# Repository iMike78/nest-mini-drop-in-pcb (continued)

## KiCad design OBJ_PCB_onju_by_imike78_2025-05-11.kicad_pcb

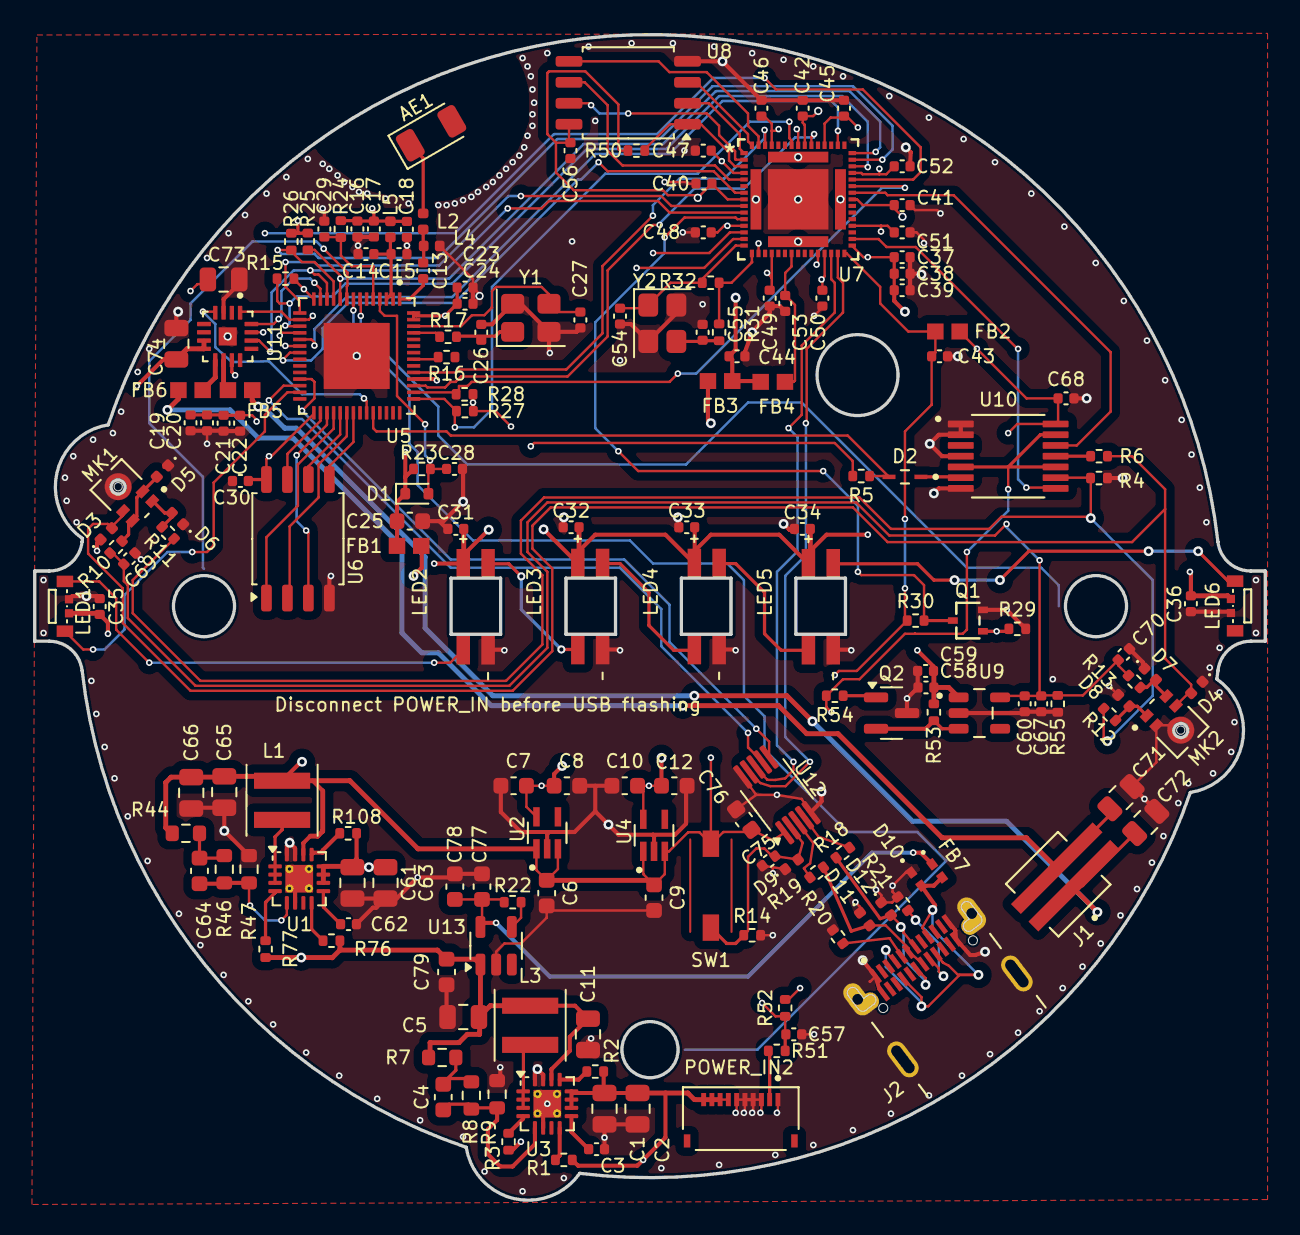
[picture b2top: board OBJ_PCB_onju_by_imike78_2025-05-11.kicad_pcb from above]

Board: 4 copper layers, 74.5 x 70.6 mm, 177 parts (0 on the bottom side), 106 nets.

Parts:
AE1: 2450AT18A100E; Johanson_2450AT18x100
C1, C5, C61, C65: 22uF; C_0805_2012Metric
C2, C63: 10uF; C_0805_2012Metric
C3, C62: 10nF; C_0402_1005Metric
C4, C64: 220pF; C_0603_1608Metric
C6, C9: 2.2uF; C_0603_1608Metric
C7, C10, C78: 4.7uF; C_0603_1608Metric
C8, C12, C25, C76, C77, C79: 100nF; C_0603_1608Metric
C11, C66, C73: 100nF; C_0805_2012Metric
C13: 1.2pF; C_0402_1005Metric
C14: 2.4pF; C_0402_1005Metric
C15, C16, C19, C20, C21, C23, C30, C31, C32, C33, C34, C35, C36, C37, C38, C39, C40, C41, C42, C43, C45, C46, C47, C48, C49, C50, C51, C52, C56, C57, C58, C67, C68, C69, C70, C75: 100nF; C_0402_1005Metric
C17, C22, C24, C28, C44, C53, C60: 1uF; C_0402_1005Metric
C18: 10uF; C_0402_1005Metric
C26, C27, C29: 12pF; C_0402_1005Metric
C54, C55: 20pF; C_0402_1005Metric
C59: 2.2uF; C_0402_1005Metric
C71, C72: 10nF; C_0805_2012Metric
C74: 47uF; C_0805_2012Metric
D1: LRB520S-30T1G; D_SOD-523
D2: RB521S30T1G; DIOM168X70N
D3, D4, D5, D6, D7, D8, D9, D11, D12: PESD0402V05; D_0402_1005Metric
D10: TPD1E10B06DPYR; TPD1E05U06DPYR
FB1, FB2: 120R; BLM18PG121SN1D
FB3, FB4, FB5, FB6: 600R; BLM18PG121SN1D
FB7: 0R; TPD1E05U06DPYR
J1: 1775443-2
J2: usb_c
L1, L3: 2.2uH; L_Coilcraft_XxL4020
L2: 3.3nH; L_0402_1005Metric
L4: 2.7nH; L_0402_1005Metric
L5: 2.2nH; L_0402_1005Metric
LED1, LED6: SK6812D-EC3210R; LED-SMD_4P_SK6812D-EC3210R
LED2, LED3, LED4, LED5: SK6812MINI-E
MK1, MK2: T3902; MIC_T3902
POWER_IN2: FH34SRJ-10S-0.5SH_50_; HRS_FH34SRJ-10S-0.5SH_50_
Q1: LBSS138WT1G; SC-70-3_L2.1-W1.3-P0.65-LS2.1-BR
Q2: BC847B; SOT-23
R1, R2, R3, R22, R30, R76, R77, R108: 100k; R_0402_1005Metric
R4, R29, R55: 47k; R_0402_1005Metric
R5, R14, R23, R24: 10k; R_0402_1005Metric
R6, R10, R11, R12, R13, R51: 100R; R_0402_1005Metric
R7, R44: 49.9R; R_0603_1608Metric
R8: 210k; R_0603_1608Metric
R9: 40k; R_0603_1608Metric
R15, R17: 0R; R_0402_1005Metric
R16: 499R; R_0402_1005Metric
R18, R19: 22R; R_0402_1005Metric
R20, R21: 5.1k; R_0402_1005Metric
R25, R26, R27, R28, R50: 4.7k; R_0402_1005Metric
R31: 680R; R_0402_1005Metric
R32: 1M; R_0402_1005Metric
R46: 100k; R_0603_1608Metric
R47: 22.1k; R_0603_1608Metric
R52: 1k; R_0402_1005Metric
R53: 470k; R_0402_1005Metric
R54: 3.3k; R_0402_1005Metric
SW1: SMXS‑01K‑TP; CHS-01TA
U1, U3: TPS62130; VQFN-16-1EP_3x3mm_P0.5mm_EP1.68x1.68mm_ThermalVias
U2: MIC5365-1.8YC5-TR; SOT65P210X110-5N
U4: MIC5365-0.9YC5-TR; SOT65P210X110-5N
U5: ESP32-S3R8; QFN40P700X700X90-57N
U6, U8: W25Q128JVSIQ; SOIC-8_5.3x5.3mm_P1.27mm
U7: XU316-1024-QF60B-C24
U9: TLV73333PDBVR
U10: SN74LVC125APWR; SOP65P640X120-14N
U11: MAX98357AETE_T; max98357aete
U12: FSUSB42MUX; MSOP-10_3x3mm_P0.5mm
U13: AP22802AW5-7; SOT-23-5
Y1: 40MHz; Crystal_SMD_3225-4Pin_3.2x2.5mm
Y2: 24MHz; Crystal_SMD_3225-4Pin_3.2x2.5mm

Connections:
+0V9: C10.1, C12.1, FB3.1, U4.5 (VOUT)
+1V8: C7.1, C8.1, C37.1, C38.1, C39.1, U2.5 (VOUT), U7.17 (VDDIOB18), U7.26 (VDDIOB18), U7.31 (USB_VDD18)
+3V3: C6.1, C9.1, C43.1, C65.1, C66.1, C76.1, FB1.1, FB2.1, L1.2, R30.1, R44.1, SW1.SI, U1.14 (VOS), U2.1 (VIN), U2.3 (EN), U4.1 (VIN), U4.3 (EN), U7.30 (USB_VDD33), U12.1 (VCC)
+5V: C5.1, C11.1, C31.1, C32.1, C33.1, C34.1, C35.1, C36.1, C58.1, C59.1, C61.1, C63.1, C73.1, C74.1, C79.1, L3.2, LED1.4 (VDD), LED2.1 (VDD), LED3.1 (VDD), LED4.1 (VDD), LED5.1 (VDD), LED6.4 (VDD), R7.1, R53.2, R76.1, R77.1, R108.1, U1.10 (VIN), U1.11 (VIN), U1.12 (VIN), U3.14 (VOS), U9.1 (IN), U11.7 (VDD), U11.8 (VDD), U13.1 (OUT)
+14V: C1.1, C2.1, POWER_IN2.7, POWER_IN2.8, POWER_IN2.9, POWER_IN2.10, R1.1, R2.1, R3.1, U3.10 (VIN), U3.11 (VIN), U3.12 (VIN)
/ESP32-S3R8/SPI_CLK: U5.33 (SPICLK), U6.6 (CLK)
/ESP32-S3R8/SPI_CS0: U5.32 (SPICS0), U6.1 (~CS)
/ESP32-S3R8/SPI_D: U5.35 (SPID), U6.5 (DI/IO_{0})
/ESP32-S3R8/SPI_HD: U5.30 (SPIHD), U6.7 (~HOLD/~RESET/IO_{3})
/ESP32-S3R8/SPI_Q: U5.34 (SPIQ), U6.2 (DO/IO_{1})
/ESP32-S3R8/SPI_WP: U5.31 (SPIWP), U6.3 (~WP/IO_{2})
/Power/USB_D_N: D12.2 (A2), J2.A7 (DN1), J2.B7 (DN2), R18.1
/Power/USB_D_P: D11.2 (A2), J2.A6 (DP1), J2.B6 (DP2), R19.1
/Power/USB_IN_D_N: R18.2, U12.4 (D-)
/Power/USB_IN_D_P: R19.2, U12.3 (D+)
/Power/USB_SEL: C75.1, D9.2 (A2), R14.1, SW1.S0, U12.2 (SEL)
/XMOS/MIC_CLK: U7.39 (X1D22), U10.12 (4A)
/XMOS/MIC_CLK_M: D3.2 (A2), D4.2 (A2), MK1.4 (CLK), MK2.4 (CLK), R6.1
/XMOS/MIC_DATA: U7.32 (X1D13), U10.8 (3Y)
/XMOS/MIC_DATA_M: R4.2, R11.1, R12.1, U10.9 (3A)
/XMOS/QSPI_CLK: U7.5 (X0D10), U8.6 (CLK)
/XMOS/QSPI_CS_N: R50.1, U7.3 (X0D01), U8.1 (~CS)
/XMOS/QSPI_D0: U7.59 (X0D04), U8.5 (DI/IO_{0})
/XMOS/QSPI_D1: U7.1 (X0D05), U8.2 (DO/IO_{1})
/XMOS/QSPI_D2: U7.60 (X0D06), U8.3 (~WP/IO_{2})
/XMOS/QSPI_D3: U7.2 (X0D07), U8.7 (~HOLD/~RESET/IO_{3})
/XMOS/VBUS_DETEC: Q1.3 (D), R30.2, U7.11 (X1D09)
AUDIO_PA_EN: U5.37 (SPICLK_P), U11.4 (SD_MODE)
ESP_3V3: C16.1, C17.1, C18.1, C19.1, C20.1, C21.1, C22.1, C23.2, C24.2, C25.1, C30.1, D1.1 (K), FB1.2, L5.2, R5.2, R23.1, R24.1, R25.1, R26.1, R27.1, R28.1, U5.20 (VDD3P3_RTC), U5.29 (VDD_SPI), U5.46 (VDD3P3_CPU), U5.55 (VDDA1), U5.56 (VDDA2), U6.8 (VCC)
ESP_BOOT: C29.1, R24.2, U5.5 (GPIO0)
ESP_IO40: U5.45 (MTDO), U7.51 (X0D43)
ESP_IO41: U5.47 (MTDI), U7.58 (X0D33)
ESP_MUTE_DET: D2.2, R5.1, U5.38 (GPIO33)
ESP_RST: C28.1, D1.2 (A), R23.2, U5.4 (CHIP_PU)
ESP_USB_N: U5.25 (GPIO19), U12.6 (HSD1-)
ESP_USB_P: U5.26 (GPIO20), U12.7 (HSD1+)
ESP_WS2812: LED1.3 (DIN), U5.27 (GPIO21)
GND: C1.2, C2.2, C3.1, C5.2, C6.2, C7.2, C8.2, C9.2, C10.2, C11.2, C12.2, C14.2, C15.2, C16.2, C17.2, C18.2, C19.2, C20.2, C21.2, C22.2, C23.1, C24.1, C25.2, C26.1, C27.1, C28.2, C29.2, C30.2, C31.2, C32.2, C33.2, C34.2, C35.2, C36.2, C37.2, C38.2, C39.2, C40.2, C41.2, C42.2, C43.2, C44.2, C45.2, C46.2, C47.2, C48.2, C49.2, C50.2, C51.2, C52.2, C53.2, C54.2, C55.2, C56.2, C57.2, C58.2, C59.2, C60.2, C61.2, C62.1, C63.2, C65.2, C66.2, C67.2, C68.2, C69.2, C70.2, C71.2, C72.2, C73.2, C74.2, C75.2, C76.2, C77.2, C78.2, C79.2, D3.1 (A1), D4.1 (A1), D5.1 (A1), D6.1 (A1), D7.1 (A1), D8.1 (A1), D9.1 (A1), D10.1 (A1), D11.1 (A1), D12.1 (A1), J2.A1 (GND_A), J2.A12 (GND_A), J2.B1 (GND_B), J2.B12 (GND_B), J2.SH1 (SHIELD), J2.SH2 (SHIELD), J2.SH3 (SHIELD), J2.SH4 (SHIELD), L4.1, LED1.1 (GND), LED2.3 (GND), LED3.3 (GND), LED4.3 (GND), LED5.3 (GND), LED6.1 (GND), MK1.3_1 (GND), MK1.3_2 (GND), MK2.2 (SELECT), MK2.3_1 (GND), MK2.3_2 (GND), POWER_IN2.1, POWER_IN2.3, POWER_IN2.4, POWER_IN2.5, POWER_IN2.6, Q1.2 (S), Q2.3 (E), R4.1, R9.2, R14.2, R20.2, R21.2, R29.2, R47.2, R55.1, U1.6 (GND), U1.15 (GND), U1.16 (GND), U1.17 (GND), U2.2 (GND), U3.6 (GND), U3.15 (GND), U3.16 (GND), U3.17 (GND), U4.2 (GND), U5.57 (GND), U6.4 (GND), U7.65 (VSS), U8.4 (GND), U9.2 (GND), U10.1 (1~OE), U10.2 (1A), U10.4 (2~OE), U10.7 (GND), U11.3 (GND), U11.11 (GND), U11.15 (GND), U11.17 (EP), U12.5 (GND), U12.10 (~OE), U13.2 (GND), Y1.2, Y1.4, Y2.2, Y2.4
I2C2_SCL: R28.2, U5.44 (MTCK), U7.40 (X0D29)
I2C2_SDA: R27.2, U5.43 (GPIO38), U7.54 (X0D30)
I2C_SCL: R26.2, U5.11 (GPIO6), U7.44 (X0D37)
I2C_SDA: R25.2, U5.10 (GPIO5), U7.45 (X0D38)
I2S2_BCLK: U5.18 (GPIO13), U7.41 (X0D35)
I2S2_DATA: U5.21 (XTAL_32K_P), U7.7 (X0D11)
I2S2_LRCLK: U5.19 (GPIO14), U7.47 (X0D39)
I2S2_MCLK: R15.1, U5.17 (GPIO12), U7.43 (X0D36)
I2S_BCLK: U5.13 (GPIO8), U7.13 (X1D10), U11.16 (BCLK)
I2S_DIN_ESP: U5.16 (GPIO11), U7.53 (X1D34), U11.1 (DIN)
I2S_DIN_SEC: U5.15 (GPIO10), U7.9 (X1D00)
I2S_LRCK: U5.12 (GPIO7), U7.10 (X1D01), U11.14 (LRCLK)
I2S_MCLK: R15.2, U5.14 (GPIO9), U7.14 (X1D11)
MUTE: POWER_IN2.2, R51.2
MUTE_ON: C57.1, R51.1, R52.1, R54.2, U10.5 (2A), U10.10 (3~OE), U10.13 (4~OE)
unnamed: AE1.1, L2.1
unnamed: C4.1, R7.2, R8.1
unnamed: C13.1, L2.2, L4.2
unnamed: C14.1, C15.1, L5.1, U5.2 (VDD3P3), U5.3 (VDD3P3)
unnamed: C26.2, R17.1, Y1.1
unnamed: C55.1, R31.2, Y2.3
unnamed: C64.1, R44.2, R46.1
unnamed: C71.1, FB6.2, J1.2
unnamed: C72.1, FB5.2, J1.1
unnamed: D5.2 (A2), MK1.2 (SELECT), MK1.5 (VDD), R10.2
unnamed: D6.2 (A2), MK1.1 (DATA), R11.2
unnamed: D7.2 (A2), MK2.5 (VDD), R13.2
unnamed: D8.2 (A2), MK2.1 (DATA), R12.2
unnamed: D10.2 (A2), FB7.2, J2.A4 (VBUS_A), J2.A9 (VBUS_A), J2.B4 (VBUS_B), J2.B9 (VBUS_B)
unnamed: J2.A5 (CC1), R20.1
unnamed: J2.B5 (CC2), R21.1
unnamed: L1.1, U1.1 (SW), U1.2 (SW), U1.3 (SW)
unnamed: L3.1, U3.1 (SW), U3.2 (SW), U3.3 (SW)
unnamed: LED1.2 (DOUT), LED2.4 (DIN)
unnamed: LED2.2 (DOUT), LED3.4 (DIN)
unnamed: LED3.2 (DOUT), LED4.4 (DIN)
unnamed: LED4.2 (DOUT), LED5.4 (DIN)
unnamed: LED5.2 (DOUT), LED6.3 (DIN)
unnamed: Q2.1 (B), R54.1
unnamed: Q2.2 (C), R53.1, U9.3 (EN)
unnamed: R76.2, U1.8 (DEF)
unnamed: R108.2, U1.13 (EN)
unnamed: C64.2, R46.2, R47.1, U1.5 (FB)
unnamed: R77.2, U1.4 (PG)
unnamed: C62.2, U1.9 (SS/TR)
unnamed: R1.2, U3.8 (DEF)
unnamed: R2.2, U3.13 (EN)
unnamed: C4.2, R8.2, R9.1, U3.5 (FB)
unnamed: R3.2, U3.4 (PG)
unnamed: C3.2, U3.9 (SS/TR)
unnamed: C13.2, U5.1 (LNA_IN)
unnamed: R16.2, U5.49 (U0TXD)
unnamed: R17.2, U5.53 (XTAL_N)
unnamed: C27.2, U5.54 (XTAL_P), Y1.3
unnamed: C53.1, FB4.1, U7.22 (PLL_AVDD)
unnamed: R31.1, R32.2, U7.16 (XIN)
unnamed: C54.1, R32.1, U7.15 (XOUT), Y2.1
unnamed: D2.1, U10.6 (2Y)
unnamed: R6.2, U10.11 (4Y)
unnamed: FB5.1, U11.10 (OUTN)
unnamed: FB6.1, U11.9 (OUTP)
unnamed: R22.1, U13.4 (EN)
VBUS: C77.1, C78.1, FB7.1, Q1.1 (G), R22.2, R29.1, U13.5 (IN)
VDD: C44.1, C45.1, C46.1, C47.1, C48.1, C49.1, C50.1, C51.1, C52.1, FB3.2, FB4.2, U7.4 (VDD), U7.12 (VDD), U7.19 (VDD), U7.27 (VDD), U7.34 (VDD), U7.42 (VDD), U7.49 (VDD), U7.57 (VDD), U7.61 (VDD), U7.62 (VDD), U7.63 (VDD), U7.64 (VDD)
VDDIO: C40.1, C41.1, C42.1, C56.1, C68.1, FB2.2, R50.2, R52.2, U7.8 (VDDIOL), U7.38 (VDDIOR), U7.52 (VDDIOT), U8.8 (VCC), U10.14 (VCC)
VDD_MIC: C60.1, C67.1, C69.1, C70.1, R10.1, R13.1, R55.2, U9.5 (OUT)
XMOS_USB_N: U7.28 (USB_DM), U12.8 (HSD2-)
XMOS_USB_P: U7.29 (USB_DP), U12.9 (HSD2+)

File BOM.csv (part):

Top Designator;Comment;Footprint;Part # ;Manufacturer;Footprint;Description;JLCPCB Part #
AE1;2450AT18A100E;Johanson_2450AT18x100;2450AT18A100E;Johanson Dielectrics;1206;0.5dBi 2.4G Antenna 2.4GHz 2W 1206 Antennas ROHS;C89334
C1,C5,C61,C65;22uF;805;CL21A226MAQNNNE;Samsung Electro-Mechanics;805;25V 22uF X5R ±20% 0805 Multilayer Ceramic Capacitors MLCC - SMD/SMT ROHS;C45783
C2,C63;10uF;805;CL21A106KAYNNNE;Samsung Electro-Mechanics;805;25V 10uF X5R ±10% 0805 Multilayer Ceramic Capacitors MLCC - SMD/SMT ROHS;C15850
C3,C62;10nF;402;CL05B103KB5NNNC;Samsung Electro-Mechanics;402;50V 10nF X7R ±10% 0402 Multilayer Ceramic Capacitors MLCC - SMD/SMT ROHS;C15195
C4,C64;220pF;603;CL10B221KB8NNNC;Samsung Electro-Mechanics;603;50V 220pF X7R ±10% 0603 Multilayer Ceramic Capacitors MLCC - SMD/SMT ROHS;C1603
C6,C9;2.2uF;603;CL10A225KO8NNNC;Samsung Electro-Mechanics;603;16V 2.2uF X5R ±10% 0603 Multilayer Ceramic Capacitors MLCC - SMD/SMT ROHS;C23630
C10,C7,C78;4.7uF;603;CL10A475KO8NNNC;Samsung Electro-Mechanics;603;16V 4.7uF X5R ±10% 0603 Multilayer Ceramic Capacitors MLCC - SMD/SMT ROHS;C19666
C11,C66,C73;100nF;805;CC0805KRX7R9BB104;YAGEO;805;50V 100nF X7R ±10% 0805 Multilayer Ceramic Capacitors MLCC - SMD/SMT ROHS;C49678
C12,C25,C76,C77,C79,C8;100nF;603;CC0603KRX7R9BB104;YAGEO;603;50V 100nF X7R ±10% 0603 Multilayer Ceramic Capacitors MLCC - SMD/SMT ROHS;C14663
C13;1.2pF;402;CC0402BRNPO9BN1R2;YAGEO;402;50V 1.2pF NP0 0402  Multilayer Ceramic Capacitors MLCC - SMD/SMT ROHS;C327292
C14;2.4pF;402;0402CG2R4C500NT;FH (Guangdong Fenghua Advanced Tech);402;50V 2.4pF C0G 0402  Multilayer Ceramic Capacitors MLCC - SMD/SMT ROHS;C48346
C15,C16,C19,C20,C21,C23,C30,C37,C38,C39,C40,C41,C42,C43,C45,C46,C47,C48,C49,C50,C51,C52,C56,C57,C58,C67,C68,C69,C70,C75;100nF;402;CL05B104KO5NNNC;Samsung Electro-Mechanics;402;16V 100nF X7R ±10% 0402 Multilayer Ceramic Capacitors MLCC - SMD/SMT ROHS;C1525
C31,C32,C33,C34,C35,C36;0.1uF;402;CL05B104KO5NNNC;Samsung Electro-Mechanics;402;16V 100nF X7R ±10% 0402 Multilayer Ceramic Capacitors MLCC - SMD/SMT ROHS;C1525
C17,C22,C24,C28,C44,C53,C60;1uF;402;CL05A105KA5NQNC;Samsung Electro-Mechanics;402;25V 1uF X5R ±10% 0402 Multilayer Ceramic Capacitors MLCC - SMD/SMT ROHS;C52923
C18;10uF;402;CL05A106MQ5NUNC;Samsung Electro-Mechanics;402;6.3V 10uF X5R ±20% 0402 Multilayer Ceramic Capacitors MLCC - SMD/SMT ROHS;C15525
C26,C27,C29;12pF;402;0402CG120J500NT;FH (Guangdong Fenghua Advanced Tech);402;50V 12pF C0G ±5% 0402 Multilayer Ceramic Capacitors MLCC - SMD/SMT ROHS;C1547
C54,C55;20pF;402;0402CG200J500NT;FH (Guangdong Fenghua Advanced Tech);402;50V 20pF C0G ±5% 0402 Multilayer Ceramic Capacitors MLCC - SMD/SMT ROHS;C1554
C59;2.2uF;402;CL05A225MQ5NSNC;Samsung Electro-Mechanics;402;6.3V 2.2uF X5R ±20% 0402 Multilayer Ceramic Capacitors MLCC - SMD/SMT ROHS;C12530
C71,C72;10nF;805;CL21B103KBANNNC;Samsung Electro-Mechanics;805;50V 10nF X7R ±10% 0805 Multilayer Ceramic Capacitors MLCC - SMD/SMT ROHS;C1710
C74;47uF;805;CL21A476MQYNNNE;Samsung Electro-Mechanics;805;6.3V 47uF X5R ±20% 0805 Multilayer Ceramic Capacitors MLCC - SMD/SMT ROHS;C16780
D1;LRB520S-30T1G;D_SOD-523;LRB520S-30T1G;LRC;SOD-523;30V 600mV 200mA SOD-523 Schottky Diodes ROHS;C83680
D2;RB521S30T1G;DIOM168X70N;RB521S30T1G;DOWO;SOD-523;SOD-523 Schottky Diodes ROHS;C27636108
D10;TPD1E10B06DPYR;TPD1E05U06DPYR;TPD1E10B06DPYR;Texas Instruments;X1-SON-2(0.6x1);90W 14V 6V 5.5V X1-SON-2(0.6x1) ESD and Surge Protection (TVS/ESD) ROHS;C48260
FB1,FB2;120R;BLM18PG121SN1D;BLM18PG121SN1D;Murata Electronics;603;50m? ±25% 120?@100MHz 0603 Ferrite Beads ROHS;C14709
FB3,FB4,FB5,FB6;600R;BLM18PG121SN1D;MPZ1608S601ATA00;TDK;603;150m? ±25% 600?@100MHz 0603 Ferrite Beads ROHS;C107335
FB7;0R;TPD1E05U06DPYR;TPD1E05U06DPYR-TP;TECH PUBLIC;DFN1006-2;DFN1006-2 ESD and Surge Protection (TVS/ESD) ROHS;C907835
J1;1775443-2;1775443-2;5-1775443-2;TE Connectivity;SMD,P=1.5mm;1 Tin 1.5mm -55?~+105? Brass 3A Standing paste SMD,P=1.5mm  Wire To Board Connector ROHS;C5162845
L1,L3;2.2uH;L_Coilcraft_XxL4020;MLZ1005M2R2WT000;TDK;402;2.2uH ±20% 60mA 550m? 0402  Inductors (SMD) ROHS;C383389
L2;3.3nH;402;VHF160808H3N3ST;FH (Guangdong Fenghua Advanced Tech);603;400mA 3.3nH 200m? 0603 Inductors (SMD) ROHS;C1029
L4;2.7nH;402;MHQ1005P2N7BT000;TDK;402;900mA 2.7nH 40m? 0402  Inductors (SMD) ROHS;C434826
L5;2.2nH;402;LQG15HS2N2B02D;Murata Electronics;402;900mA 2.2nH 90m? 0402 Inductors (SMD) ROHS;C162540
LED1,LED6;SK6812D-EC3210R;LED-SMD_4P_SK6812D-EC3210R;SK6812D-EC3210R;OPSCO Optoelectronics;SMD,1.1x3.2mm;SMD,1.1x3.2mm  RGB LEDs(Built-in IC) ROHS;C2890041
LED2,LED3,LED4,LED5;SK6812MINI-E;SK6812MINI-E;SK6812MINI-E;OPSCO Optoelectronics;SMD;SMD RGB LEDs(Built-in IC) ROHS;C5149201
MK1,MK2;T3902;MIC_T3902;MMICT390200012;TDK InvenSense;-;Omni-directional -32dB 64dB -  MEMS Microphones ROHS;C3171752
POWER_IN2;FH34SRJ-10S-0.5SH_50_;HRS_FH34SRJ-10S-0.5SH_50_;FH34SRJ-10S-0.5SH(50);HRS(Hirose);SMD,P=0.5mm,??;-55?~+105? 10P Dual-sided contacts / top and bottom connection Horizontal attachment 0.5mm SMD,P=0.5mm,Surface Mount?Right Angle FFC, FPC (Flat Flexible) Connector Assemblies ROHS;C324723
Q1;LBSS138WT1G;SC-70-3_L2.1-W1.3-P0.65-LS2.1-BR;LBSS138WT1G;LRC;SC-70;50V 200mA 3.5?@5V,200mA 150mW 1.5V 1 N-Channel SC-70 MOSFETs ROHS;C383201
Q2;BC847B;SOT-23;BC847B;hongjiacheng;SOT-23;45V 200mW 200@2.0mA,5.0V 100mA NPN SOT-23  Bipolar (BJT) ROHS;C20069135
R1,R108,R2,R22,R3,R30,R76,R77;100k;402;RC0603FR-07100KL;YAGEO;603;100mW Thick Film Resistors 75V ±100ppm/? ±1% 100k? 0603 Chip Resistor - Surface Mount ROHS;C14675
R8;210k;603;0603WAF2103T5E;UNI-ROYAL(Uniroyal Elec);603;100mW Thick Film Resistors 75V ±100ppm/? ±1% 210k? 0603 Chip Resistor - Surface Mount ROHS;C22952
R9;40k;603;RT0603BRD0740KL;YAGEO;603;100mW Thin Film Resistor ±25ppm/? ±0.1% 40k? 0603  Chip Resistor - Surface Mount ROHS;C861392
R10,R11,R12,R13,R51,R6;100R;402;0402WGF1000TCE;UNI-ROYAL(Uniroyal Elec);402;62.5mW Thick Film Resistors 50V ±1% ±200ppm/? 100? 0402 Chip Resistor - Surface Mount ROHS;C25076
R14,R23,R24,R5;10k;402;0402WGF1002TCE;UNI-ROYAL(Uniroyal Elec);402;62.5mW Thick Film Resistors 50V ±100ppm/? ±1% 10k? 0402 Chip Resistor - Surface Mount ROHS;C25744
R15,R17;0R;402;0402WGF0000TCE;UNI-ROYAL(Uniroyal Elec);402;62.5mW Thick Film Resistors 50V ±800ppm/? ±1% 0? 0402 Chip Resistor - Surface Mount ROHS;C17168
R16;499R;402;RC0402FR-07499RL;YAGEO;402;62.5mW Thick Film Resistors 50V ±100ppm/? ±1% 499? 0402 Chip Resistor - Surface Mount ROHS;C137970
R18,R19;22R;402;0402WGF220JTCE;UNI-ROYAL(Uniroyal Elec);402;62.5mW Thick Film Resistors 50V ±1% ±100ppm/? 22? 0402 Chip Resistor - Surface Mount ROHS;C25092
R20,R21;5.1k;402;0402WGF5101TCE;UNI-ROYAL(Uniroyal Elec);402;62.5mW Thick Film Resistors 50V ±100ppm/? ±1% 5.1k? 0402 Chip Resistor - Surface Mount ROHS;C25905
R25,R26,R27,R28,R50;4.7k;402;0402WGF4701TCE;UNI-ROYAL(Uniroyal Elec);402;62.5mW Thick Film Resistors 50V ±100ppm/? ±1% 4.7k? 0402 Chip Resistor - Surface Mount ROHS;C25900
R29,R4,R55;47k;402;0402WGF4702TCE;UNI-ROYAL(Uniroyal Elec);402;62.5mW Thick Film Resistors 50V ±100ppm/? ±1% 47k? 0402 Chip Resistor - Surface Mount ROHS;C25792
R31;680R;402;0402WGF6800TCE;UNI-ROYAL(Uniroyal Elec);402;62.5mW Thick Film Resistors 50V ±100ppm/? ±1% 680? 0402 Chip Resistor - Surface Mount ROHS;C25130
R32;1M;402;0402WGF1004TCE;UNI-ROYAL(Uniroyal Elec);402;62.5mW Thick Film Resistors 50V ±100ppm/? ±1% 1M? 0402 Chip Resistor - Surface Mount ROHS;C26083
R44,R7;49.9R;603;0603WAF499JT5E;UNI-ROYAL(Uniroyal Elec);603;100mW Thick Film Resistors 75V ±100ppm/? ±1% 49.9? 0603 Chip Resistor - Surface Mount ROHS;C23185
R46;100k;603;0603WAF1003T5E;UNI-ROYAL(Uniroyal Elec);603;100mW Thick Film Resistors 75V ±100ppm/? ±1% 100k? 0603 Chip Resistor - Surface Mount ROHS;C25803
R47;22.1k;603;0603WAF2212T5E;UNI-ROYAL(Uniroyal Elec);603;100mW Thick Film Resistors 75V ±100ppm/? ±1% 22.1k? 0603 Chip Resistor - Surface Mount ROHS;C25961
R52;1k;402;0402WGF1001TCE;UNI-ROYAL(Uniroyal Elec);402;62.5mW Thick Film Resistors 50V ±100ppm/? ±1% 1k? 0402 Chip Resistor - Surface Mount ROHS;C11702
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
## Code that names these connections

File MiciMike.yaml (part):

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
i2c:
  - id: internal_i2c
    sda: GPIO5
    scl: GPIO6
    frequency: 400kHz

psram:
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    id: hardware_mute_switch
    internal: true
    pin:
      number: GPIO33
      mode: INPUT_PULLUP
    on_press:
      # Play mute on sound only if software mute isn't enabled
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      - microphone.unmute:
  - platform: esp32_touch
    id: volume_down
    pin: GPIO4
    threshold: 539000
    on_press:
      then:
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
  - platform: esp32_touch
    id: volume_up
    pin: GPIO2
    threshold: 580000
    on_press:
      then:
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  # Hardware LED ring. Not used because remapping needed
  - platform: esp32_rmt_led_strip
    id: leds_internal
    pin: GPIO21
    chipset: SK6812
    max_refresh_rate: 15ms
    num_leds: 6
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voice_kit:
  id: voice_kit_component
  i2c_id: internal_i2c
  reset_pin: GPIO4
  firmware:
    url: https://github.com/esphome/voice-kit-xmos-firmware/releases/download/v1.3.1/ffva_v1.3.1_upgrade.bin
    version: "1.3.1"
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
i2s_audio:
  - id: i2s_output
    # i2s_output data pin is gpio10
    i2s_lrclk_pin:
      number: GPIO7
    i2s_bclk_pin:
      number: GPIO8

  - id: i2s_input
    # data line is GPIO15
    i2s_lrclk_pin:
      number: GPIO14
    i2s_bclk_pin:
      number: GPIO13

microphone:
  - platform: i2s_audio
    id: i2s_mics
    i2s_din_pin: GPIO15
    adc_type: external
    pdm: false
    sample_rate: 16000
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    id: i2s_audio_speaker
    sample_rate: 44100
    i2s_mode: secondary
    i2s_dout_pin: GPIO10
    bits_per_sample: 16bit
    i2s_audio_id: i2s_output
    dac_type: external
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
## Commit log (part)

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2025-06-02 Update README.md
    ReadME v1
2025-06-02 Add files via upload
    1st upload of the project files
2025-06-02 Create LICENCE
    CERN-OHL-S v2.0
2025-06-02 Update README.md
    licence reference added
2025-06-02 Parts in the project
2025-06-02 Rename 1775443-2.kicad_mod to parts/1775443-2.kicad_mod
2025-06-02 Create layout
2025-06-02 Rename image.png to layout.png
2025-06-05 Update README.md
    Update README.md
2025-06-05 Reformat the PCB file without changing anything
2025-06-05 Assign +0V9, +14V and +1V8 to "power" net class
2025-06-05 Route a few more miscellancous connections
2025-06-05 Route LED connections
2025-06-05 Route a new more miscellaneous connections
2025-06-05 Add "led" net class
2025-06-11 Update README.md
    Mention the dual I2S bus under HW specs.
2025-06-15 Github desktop implemented
2025-06-15 routing ongoing
2025-06-15 routing update
2025-06-16 pic update
2025-06-18 routing finished
2025-06-18 DRC done
2025-06-19 production preparation
2025-06-20 final touches
2025-06-23 project name change
    Just removed the "onju" part from the name to avoid any issue with Justin, and state that thist is the V2 replacement board
2025-06-23 final pics
2025-06-23 name uipdate
2025-06-24 modifications for manufacturing
2025-06-24 removed unneccesary files
2025-07-05 Remove ignored files
2025-07-18 rev2 update
2025-07-29 Update README.md
    Added the ”MiciMike” codename/nickname printed on the board.
2025-07-31 Ko-fi link going to wrong account!
2025-08-01 Ko-fi link going to wrong account! (#26)
2025-08-07 Update README.md with MiciMike name and link to the Google Home Mini sister-project
    Update README.md with MiciMike name and link to the Google Home Mini sister-project
2025-08-07 Update README.md with specs for MEMS microphones and RGB LED components
    Add specs for both MEMS microphones and RGB LED components to the list of known hardware specifications in readme file:
    ```
    - 2x MEMS microphones (dual MSM261DHP with 68mm inter-mic spacing)
    - 4x SK6812 RGB LEDs
    ```
    Replaces PR https://github.com/iMike78/nest-mini-drop-in-pcb/pull/19
2025-08-10 update for production
2025-08-18 Add prototype image to README.md
    Add prototype image to README.md
2025-08-18 Adding two prototype images from iMike78
    Adding two prototype images from iMike78
2025-08-18 Second prototype picture showing it mounted
    Second prototype picture showing it mounted
2025-08-18 Add prototype 3D CAD image to readme as well
    Add prototype 3D CAD image to readme as well
2025-08-28 fixing errors
2025-09-01 Update README.md with specs for MEMS microphones and RGB LED components
    Add specs for both MEMS microphones and RGB LED components to the list of known hardware specifications in readme file.
    Replaces old PR https://github.com/iMike78/nest-mini-drop-in-pcb/pull/29
2025-10-05 Auto-translate README and Wiki
2025-10-11 ESP32 and XMOS have own SPI flash
    Clearify that ESP32 and XMOS each have their own SPI flash
2025-10-11 Update README.md
    Updates in hardware
2026-02-12 complete redesign
2026-02-28 work in progress
2026-03-05 Fix ( Spelling ): Minor spelling error in README fix.
2026-03-17 Update README mention Home Mini campaign
    Updated README to mention crowdfunding campaign for Google Home Mini PCB
2026-03-19 Revise README hardware spec replacing MAX98357A with TAS5805M
    Revise README hardware spec replacing MAX98357A with TAS5805M based on discussions:
    * https://github.com/iMike78/nest-mini-drop-in-pcb/discussions/16
    and
    https://github.com/rauli2780/nest-audio-pcb/discussions/7
    @iMike78 Note! Be aware that TAS5805M is more compex and also require a I2C connection to configure the DSP, so it not enough to just use I2S. For reference see Esparagus Audio Brick:
    * https://github.com/sonocotta/esparagus-media-center/
2026-04-28 Revise README for crowdfunding and project updates
    Updated the README to reflect ongoing crowdfunding campaign and project details.
2026-05-02 preparing for the test batch
2026-05-10 v2 hardware revision
    MPR121 touch controller added to replace the esp32-s3 internal touch interface
2026-05-16 v2 hardware
2026-05-30 Revise hardware details in README.md
    Updated hardware specifications and details for the project.
2026-05-30 Remove outdated language section from README
